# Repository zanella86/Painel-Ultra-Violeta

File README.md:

# Painel-Ultra-Violeta
Painel de LEDs UV para auxiliar na confecção de Placas de Circuito Impresso (processo fotorresistente) e cura da tinta protetora/isolante.

Características:

-PCI com 200x200(mm);

-36 Leds UV de 5mm: 3,3V 40mA (separados em 25mm entre si);

-12 resistores de 56ohms 1/8W (compatibilidade com 1/4W);

-Alimentação em 12V em uma das opções: Conectores "JST macho" ou "Borner com parafuso";

-Consumo total previsto em 1.44A;

-4 vias passantes para fixação (8mm x 3mm).

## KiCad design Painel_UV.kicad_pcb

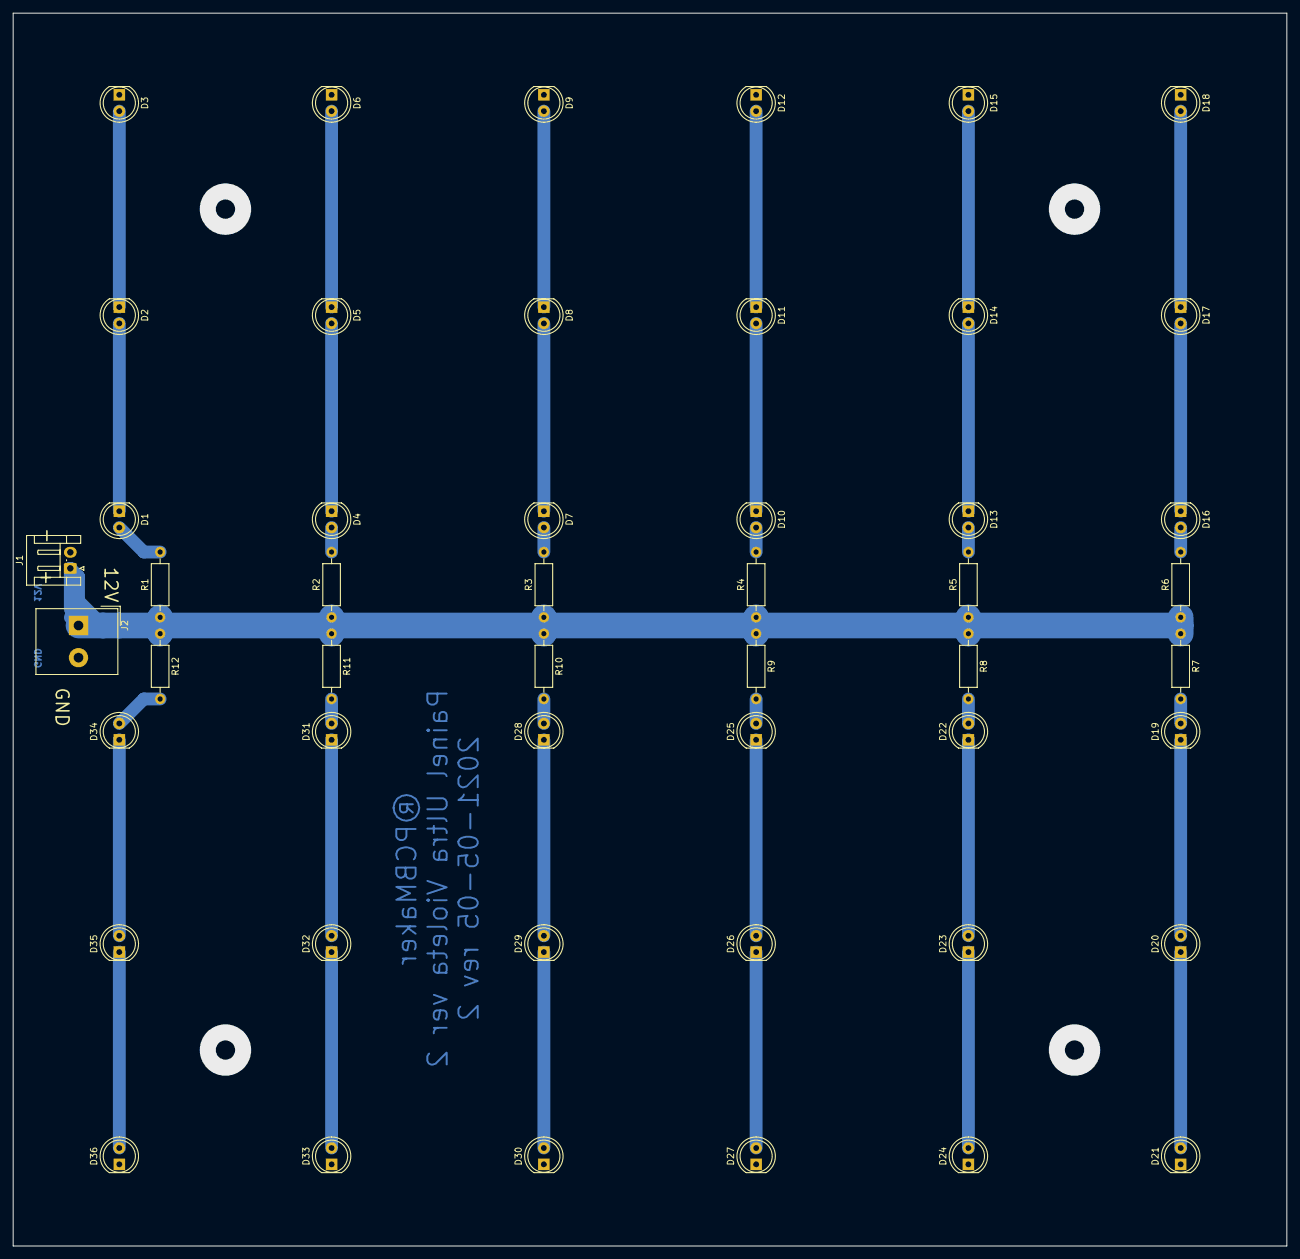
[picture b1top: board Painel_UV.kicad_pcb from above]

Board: 2 copper layers, 198.1 x 191.8 mm, 50 parts (0 on the bottom side), 38 nets.

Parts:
D1, D2, D3, D4, D5, D6, D7, D8, D9, D10, D11, D12, D13, D14, D15, D16, D17, D18, D19, D20, D21, D22, D23, D24, D25, D26, D27, D28, D29, D30, D31, D32, D33, D34, D35, D36: LED; LED_D5.0mm
J1: Conn_01x02_Male; JST_EH_S2B-EH_1x02_P2.50mm_Horizontal
J2: Screw_Terminal_01x02; Altech_AK300_1x02_P5.00mm_45-Degree
R1, R2, R3, R4, R5, R6, R7, R8, R9, R10, R11, R12: 56; R_Axial_DIN0207_L6.3mm_D2.5mm_P10.16mm_Horizontal

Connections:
/GND: D3.1, D6.1, D9.1, D12.1, D15.1, D18.1, D21.1, D24.1, D27.1, D30.1, D33.1, D36.1, J1.2, J2.2
/VCC: J1.1, J2.1, R1.1, R2.1, R3.1, R4.1, R5.1, R6.1, R7.1, R8.1, R9.1, R10.1, R11.1, R12.1
unnamed: D1.1, D2.2
unnamed: D1.2, R1.2
unnamed: D2.1, D3.2
unnamed: D4.1, D5.2
unnamed: D4.2, R2.2
unnamed: D5.1, D6.2
unnamed: D7.1, D8.2
unnamed: D7.2, R3.2
unnamed: D8.1, D9.2
unnamed: D10.1, D11.2
unnamed: D10.2, R4.2
unnamed: D11.1, D12.2
unnamed: D13.1, D14.2
unnamed: D13.2, R5.2
unnamed: D14.1, D15.2
unnamed: D16.1, D17.2
unnamed: D16.2, R6.2
unnamed: D17.1, D18.2
unnamed: D19.1, D20.2
unnamed: D19.2, R7.2
unnamed: D20.1, D21.2
unnamed: D22.1, D23.2
unnamed: D22.2, R8.2
unnamed: D23.1, D24.2
unnamed: D25.1, D26.2
unnamed: D25.2, R9.2
unnamed: D26.1, D27.2
unnamed: D28.1, D29.2
unnamed: D28.2, R10.2
unnamed: D29.1, D30.2
unnamed: D31.1, D32.2
unnamed: D31.2, R11.2
unnamed: D32.1, D33.2
unnamed: D34.1, D35.2
unnamed: D34.2, R12.2
unnamed: D35.1, D36.2

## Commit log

2021-05-05 Update README.md
    Inclusão de imagens do modelo em 3D.
2021-05-06 Esquema elétrico do Painel UV utilizando o método de alimentação DC em 12V (conforme descrito em #1)
2021-05-06 (#3) Painel desenvolvido em 200x200(mm) com espaço de 25mm entre os LEDS
2021-05-09 #7 e #8: Gerada a lista de materiais utilizando o plugin bom2grouped_csv
2021-05-09 Update README.md
    Inclusão das características do projeto.
2021-08-15 Update README.md
    Incluído as medidas dos furos passantes e dos LEDs.
